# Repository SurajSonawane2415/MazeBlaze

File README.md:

# MazeBlaze
Develop a Line following and Maze Solving bot based on PID controller that can find the shortest path in a given maze.

## Table of Contents

- [Project](#project)
   - [Table of Contents](#table-of-contents)
   - [About The Project](#about-the-project)
   - [PCB MODEL](#pcb-model)
   - [Demo](#demo)
   - [File Structure](#file-structure)
   - [Getting started](#getting-started)
   - [Future Work](#future-work)
   - [Contributors](#contributors)
   - [Resources](#resources)
   - [Acknowledgements](#acknowledgements)
   - [License](#license)

## About The Project
In this project, we will create a Line-following, Maze-solving bot that can find the shortest path in the given maze.

## Domains Explored
Artificial Intelligence, Embedded C, Control Systems, Graph Algorithms, Electronics and PCB Design

## Project Workflow
- Learning firmware development by completing [Firmware task](https://github.com/SurajSonawane2415/MazeBlaze/tree/main/task/suraj/firmware). And we also understand the firmware used in [SRA Wall-E](https://github.com/SRA-VJTI/Wall-E) and [MazeBlaze-v2](https://github.com/PritK99/MazeBlaze).
- Learning PCB design by completing the line sensor array [pcb_design](https://github.com/SurajSonawane2415/MazeBlaze/tree/main/task/suraj/pcb%20design) task.
- For bot design improvement we created a detailed sheet to make the bot design better. In which we added the advantages and disadvantages of many designs we've reviewed and chosen the best design for the MazeBlaze-v3 bot.
- PCB Design for MazeBlaze-v3 by considering all points to make the bot design better.
- Implementing left follow rule.
- Implementing path planning.
- Implementing dijkstra's algorithm.
- Implementing flood-fill algorithm.
## PCB MODEL

## Demo
### LFR algorithm(Left follow rule):

https://github.com/SurajSonawane2415/MazeBlaze/assets/129578177/a419bddd-6653-45e9-b566-6e79a6069aff

### Dijkstra's algorithm:

https://github.com/SurajSonawane2415/MazeBlaze/assets/129578177/57cf2437-57e8-468f-b269-db0ec31de83d

## File Structure

```
👨‍💻MazeBlaze-v3.1
├ 📂 Firmware
| └ 📂1_left_follow_rule //Contains code for left-follow-rule and path planning
| | ├ 📂main
| | |   ├ 📄1_left_follow_rule.c
| | |   └ 📄CMakeList.txt
| | ├ 📄CMakeList.txt
| ├ 📂2_Dijkstra //Contains code for dijkstra`s algorithm   
| └ 📂Components //Contains all the header and source files used in the project
|   ├ 📂include
|   ├ 📂src
|   ├ 📂esp-wifi-logger
|   ├ 📄CMakeList.txt
├ 📂 assets
├ 📂 documentation //Contains documentation of the project.
├ 📂 pcb_design //Contains pcb_design files of MazeBlaze-v3 board
├ 📂 task
  ├ 📂 Atharv
  | ├ 📂 firmware 
  | |  └📂 1_led_blink.c
  | |    ├ 📂main
  | |    |   ├ 📄1_led_blink.c
  | |    |  └ 📄CMakeList.txt
  | |    ├ 📄CMakeList.txt
  | ├ 📂 pcb_design
  ├ 📂 Suraj
    ├ 📂 firmware //Conatins led blink task files and documentation of the task
    |  └📂 1_led_blink.c 
    |    ├ 📂main
    |    |   ├ 📄1_led_blink.c
    |    |   └ 📄CMakeList.txt
    |    ├ 📄CMakeList.txt
    |    ├ 📄README.md
    ├ 📂 pcb_design //Conatins lsa PCB design task files and documentation of the task
```
## Getting started
### Prerequisites
To download and use this code, the minimum requirements are:
- ESP_IDF
- Windows 7 or later (64-bit), Ubuntu 20.04 or later
- Microsoft VS Code or any other IDE

### Installation
Clone the project by typing the following command in your Terminal/CommandPrompt:
      
     `git clone https://github.com/SurajSonawane2415/MazeBlaze`

Navigate to the MazeBlaze folder:
`cd MazeBlaze`

### Usage

Once the requirements are satisfied, you can easily download the project and use it on your machine. After following the above steps, use the following commands to:

To activate the IDF:
`get_idf`

To build the code:
`idf.py build`

To flash the code:
`idf.py -p (PORT) flash monitor`

## Future Work
- [ ] Implementing better algorithms like DFS/BFS.
- [ ] Achieve higher speeds by increasing the efficiency of the bot.

## Contributors
- [Suraj Sonawane](https://github.com/SurajSonawane2415)
- [Atharva Nerkar](https://github.com/ARN1954)

## Resources
- [MazeBlaze-v2](https://github.com/PritK99/MazeBlaze) GitHub repository of MazeBlaze-v2 
- [MazeBlaze-v1](https://github.com/ChinmayLonkar/MAZEBLAZE) GitHub repository of MazeBlaze-v1
- [Dikstra's](https://www-geeksforgeeks-org.cdn.ampproject.org/v/s/www.geeksforgeeks.org/printing-paths-dijkstras-shortest-path-algorithm/amp/?usqp=mq331AQIUAKwASCAAgM%3D&amp_js_v=a9&amp_gsa=1#referrer=https%3A%2F%2Fwww.google.com&csi=1&ampshare=https%3A%2F%2Fwww.geeksforgeeks.org%2Fprinting-paths-dijkstras-shortest-path-algorithm%2Famp%2F%23referrer%3Dhttps%253A%252F%252Fwww.google.com%26csi%3D1%26ampshare%3Dhttps%253A%252F%252Fwww.geeksforgeeks.org%252Fprinting-paths-dijkstras-shortest-path-algorithm%252F) Implementation of dijkstr's algorithm in c.
- [Floodfill](https://github.com/Isuru-Dissanayake/piccola) Implementation of the Floodfill algorithm (simulation).

## Acknowledgements 
- [SRA VJTI](https://sravjti.in/) Eklavya 2023
- Special thanks to our mentors [Raj Gupta](https://github.com/RajGupta17), [Prit Kanadiya](https://github.com/PritK99), and all the seniors at SRA, VJTI for their constant support and guidance throughout the project.

## License
[MIT License](https://opensource.org/license/mit/)

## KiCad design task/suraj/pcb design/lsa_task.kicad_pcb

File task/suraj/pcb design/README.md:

# PCB Design Task:
In this task I designed a PCB for line sensor array(LSA) used in [SRA board](https://github.com/SRA-VJTI/sra-board-hardware-design). 
## Board images:
- Front side:
  
- Back side:

## Routing:
For routing of the control circuitry and power connections we used traces of 0.3mm width.
- Back copper routing

## Overview:
The Line Sensor Array (LSA) uses TCRT 5000 sensors to detect white and black lines on the surface. It then sends this data to the ESP-32 microcontroller. By analyzing and processing the data, the microcontroller ESP-32 accomplishes the task of line following.

## TCRT 5000
The TCRT 5000 is an optical sensor module commonly used for detecting the presence of objects or lines. It consists of an infrared (IR) emitter and a phototransistor. The emitter emits infrared light, which bounces off objects or surfaces and is detected by the phototransistor. The amount of reflected light is used to determine the proximity of an object or the presence of a surface, typically a white or black line. TCRT 5000 sensors are often employed in applications like line-following bot.

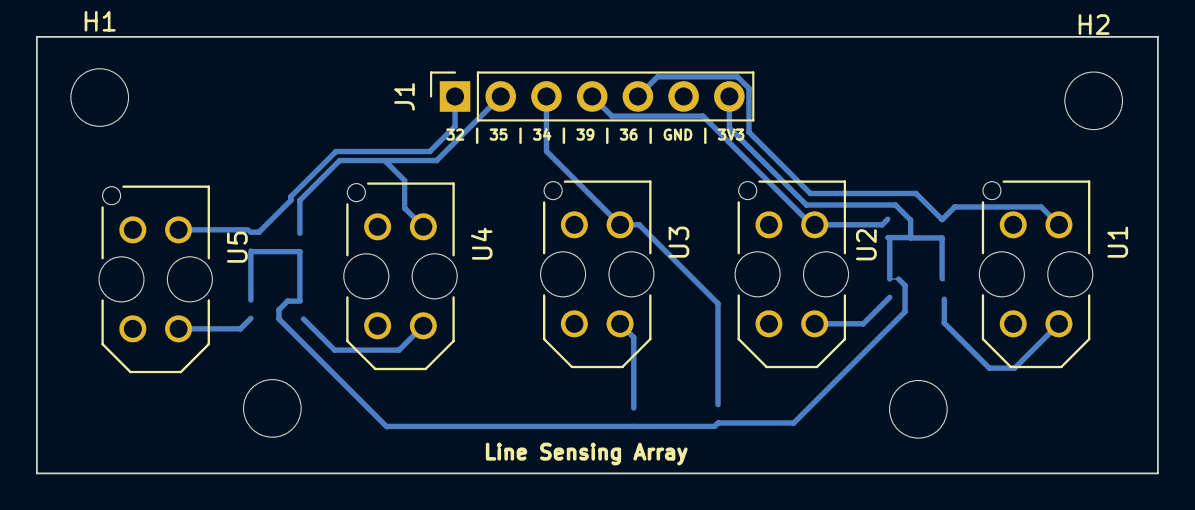
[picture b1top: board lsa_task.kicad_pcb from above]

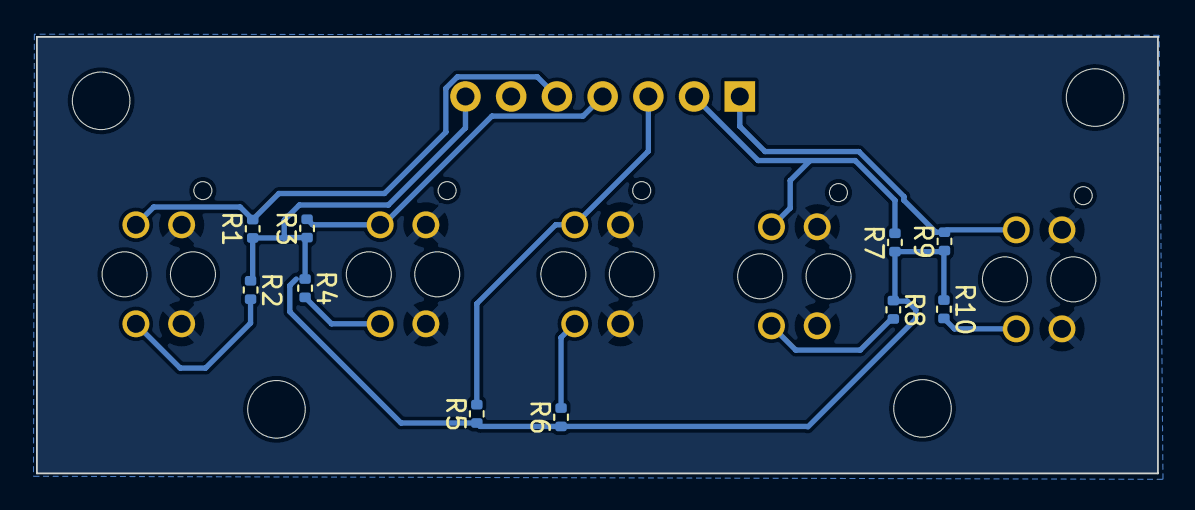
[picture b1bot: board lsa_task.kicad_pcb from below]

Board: 2 copper layers, 62.3 x 24.2 mm, 20 parts (10 on the bottom side), 12 nets.

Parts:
H1, H2, H3, H4: MountingHole_Pad; MountingHole_3.2mm_M3
J1: Conn_01x07_Pin; PinSocket_1x07_P2.54mm_Vertical
R1, R3, R5, R7, R9: 4k7; R_0402_1005Metric
R2, R4, R6, R8, R10: 1K; R_0402_1005Metric
U1, U2, U3, U4, U5: TCRT5000; OPTO_TCRT5000

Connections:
3V3: J1.7, R1.1, R2.1, R3.1, R4.1, R5.1, R6.1, R7.1, R8.1, R9.1, R10.1
A0_36: J1.5, R1.2, U1.COLL
A1_39: J1.4, R3.2, U2.COLL
A2_34: J1.3, R5.2, U3.COLL
A3_35: J1.2, R7.2, U4.COLL
A4_32: J1.1, R9.2, U5.COLL
GND: J1.6, U1.CATH, U1.E, U2.CATH, U2.E, U3.CATH, U3.E, U4.CATH, U4.E, U5.CATH, U5.E
unnamed: R2.2, U1.A
unnamed: R4.2, U2.A
unnamed: R6.2, U3.A
unnamed: R8.2, U4.A
unnamed: R10.2, U5.A

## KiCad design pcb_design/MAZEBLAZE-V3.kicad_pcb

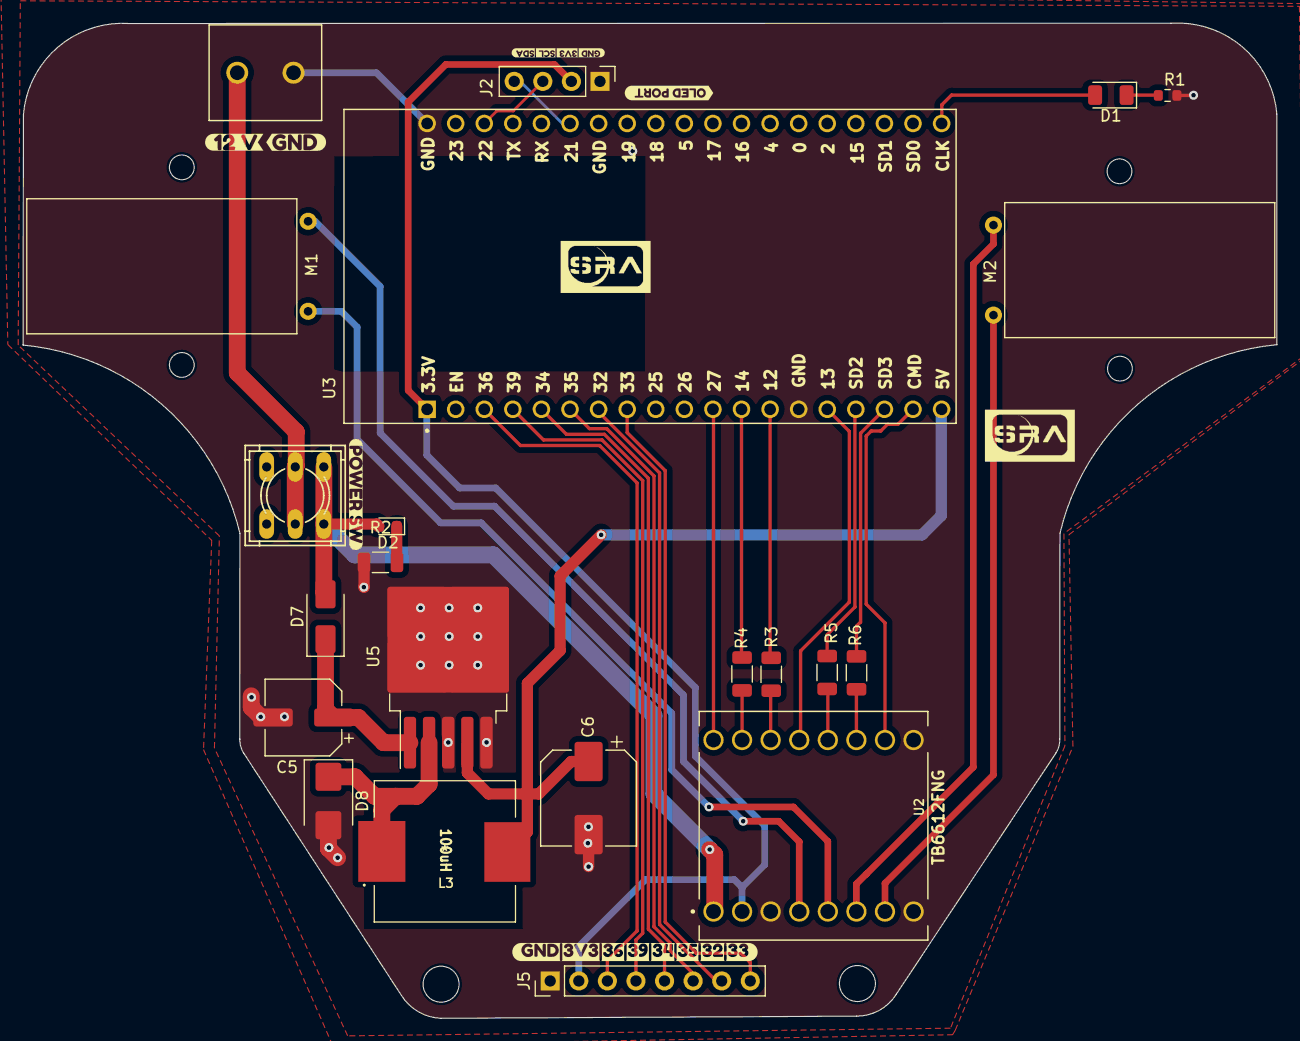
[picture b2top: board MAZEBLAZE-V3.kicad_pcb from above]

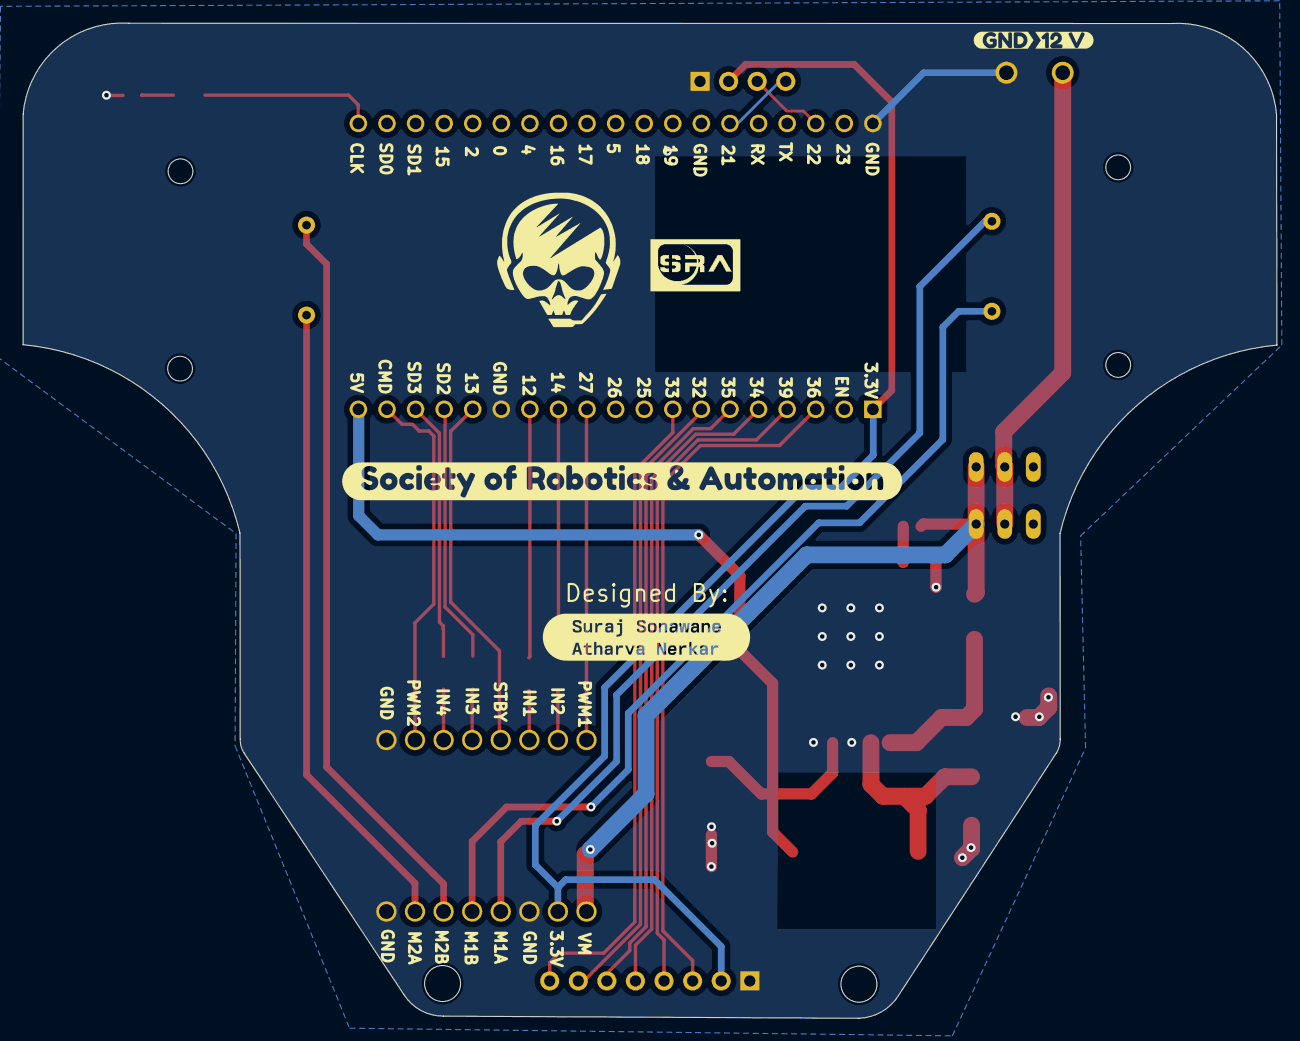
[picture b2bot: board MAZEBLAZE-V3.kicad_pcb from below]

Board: 2 copper layers, 111.4 x 88.4 mm, 38 parts (4 on the bottom side), 33 nets.

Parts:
12V_SW1: SW_Push_DPDT; dpdt_sw_2x03_tht
C5: 100uF; CP_Elec_6.3x7.7
C6: 470uF; CP_Elec_8x10
D1: RED-LED; LED_1206_3216Metric
D2: BLUE-POWER-LED; LED_0603_1608Metric
D7: SS24; D_SMA
D8: SS34; D_SMB
H1, H2#2, H3, H4: MountingHole; MountingHole_2.2mm_M2
H2, H5: MountingHole; MountingHole_3.2mm_M3
J1: Screw_Terminal_01x02; 12V_1x02_tht
J2: Conn_01x04_Pin; PinHeader_1x04_P2.54mm_Vertical
J5: Conn_01x08_Pin; PinHeader_1x08_P2.54mm_Vertical
L3: 100uH; CDRH127_inductor_smd
M1, M2: Motor_DC; N20_Motor
R1: 330; R_0603_1608Metric
R2: 1k5; R_1206_3216Metric
R3, R4, R5, R6: 1k; R_1206_3216Metric
U2: TB6612FNG; TB6612FNG_2
U3: ESP32-DEVKITC-32D; MODULE_ESP32-DEVKITC-32D
U5: LM2576S-5; TO-263-5_TabPin3
kibuzzard-61F7FB1D: G***; kibuzzard-61F7FB1D
kibuzzard-61F7FBA3: G***; kibuzzard-61F7FBA3
kibuzzard-61F7FBC2: G***; kibuzzard-61F7FBC2
kibuzzard-61F7147A: G***; kibuzzard-61F7147A
kibuzzard-61F71491: G***; kibuzzard-61F71491
kibuzzard-637A1A13: G***; kibuzzard-637A1A13
kibuzzard-653BE6A4: G***; kibuzzard-653BE6A4
kibuzzard-653BE7A2: G***; kibuzzard-653BE7A2
kibuzzard-653BEE79: G***; kibuzzard-653BEE79
kibuzzard-653E5949: G***; kibuzzard-653E5949

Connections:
3V3: J2.2, J5.2, U2.2 (VCC), U3.J2-1 (3V3)
5V: C6.1, L3.2, U3.J2-19 (EXT_5V), U5.4 (FB)
AIN1: R3.1, U3.J2-13 (IO12)
AIN2: R4.1, U3.J2-12 (IO14)
BIN1: R5.1, U3.J2-16 (SD2)
BIN2: R6.1, U3.J2-17 (SD3)
GND: C5.2, C6.2, D8.2 (A), J1.2, J2.1, J5.1, R1.2, R2.2, U2.3 (GND), U2.8 (GND), U2.9 (GND), U3.J2-14 (GND1), U3.J3-1 (GND3), U5.3 (GND), U5.5 (~ON/OFF)
IO23: D1.2 (A), U3.J3-19 (CLK)
unnamed: D1.1 (K), R1.1
unnamed: D2.1 (K), R2.1
unnamed: C5.1, D7.1 (K), U5.1 (VIN)
unnamed: D8.1 (K), L3.1, U5.2 (OUT)
unnamed: M1.1 (+), U2.4 (A01)
unnamed: M1.2 (-), U2.5 (A02)
unnamed: M2.1 (+), U2.7 (B01)
unnamed: M2.2 (-), U2.6 (B02)
unnamed: R3.2, U2.14 (AI1)
unnamed: R4.2, U2.15 (AI2)
unnamed: R5.2, U2.12 (BI1)
unnamed: R6.2, U2.11 (BI2)
PWMA: U2.16 (PWMA), U3.J2-11 (IO27)
PWMB: U2.10 (PWMB), U3.J2-18 (CMD)
SCL: J2.3, U3.J3-3 (IO22)
SDA: J2.4, U3.J3-6 (IO21)
SENS1: J5.3, U3.J2-3 (SENSOR_VP)
SENS2: J5.4, U3.J2-4 (SENSOR_VN)
SENS3: J5.5, U3.J2-5 (IO34)
SENS4: J5.6, U3.J2-6 (IO35)
SENS5: J5.7, U3.J2-7 (IO32)
SENS6: J5.8, U3.J2-8 (IO33)
STBY: U2.13 (STBY), U3.J2-15 (IO13)
VIN: 12V_SW1.2 (B), 12V_SW1.5 (B), J1.1
VIN_SW: 12V_SW1.3 (C), 12V_SW1.6 (C), D2.2 (A), D7.2 (A), U2.1 (VM)

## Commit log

2023-08-25 Rename Tasks/LFR Task/main.c to Tasks/Suraj/LFR_Task/main/main.c
2023-08-27 Create Tasks
2023-08-29 29 Aug 2023 EOD main.c
2023-08-30 30 AUG EOD main.c
2023-08-30 30 AUG EOD
    getting problem when node is detect. so to tacking left turn it goies into if statement. but for only one time
2023-09-06 Create main
2023-09-06 Update LFR.c
    updated left turn condition
2023-09-07 7 SEP EOD added extra condition for node detection.. and improve code.. but still bot not tacking turn and stop stabelly at a higher speed so extra condition needed
    7 SEP EOD added extra condition for node detection.. and improve code.. but still bot not tacking turn and stop stabelly at a higher speed so extra condition needed
2023-09-09 Only Right node condition is added
2023-09-10 Updated U turn logic and removed current reading function.. but bot not working stabelly
    Updated U turn(working properly) logic and removed current reading function.. but bot not working stabelly
2023-09-12 added LSA readings function before correction function in code. because bot not taking current readings for PID control
2023-09-13 Update LFR.c
    added LSA readings function before correction function in code. and removed unwanted 10 ms delay
2023-09-21 Counter method
2023-09-22 Updated Counter Method
2023-09-24 working code for all nodes
2023-09-24 Update code for all nodes
2023-09-25 Create simplify_path.c
    simplify path code
2023-09-26 Store path in array code
2023-09-27 Update simplify_path.c
    31 replaces by size
2023-09-27 Update LFR.c
    added simplify path condition and end condition
2023-09-29 Updated code with boot button function
2023-10-01 Updated final run code
2023-10-01 Updated final run function
2023-10-17 Update Final run code
    Tested code of full maze.
2023-10-20 Create Readme.md
    Started with documention
2023-10-20 Rename led_main.c to led_main.c
2023-10-21 Added errors description with solution
2023-10-21 Rename
2023-10-21 Create lsa
2023-10-22 code by using VISITED AND PARENT MATRIX
2023-10-23 Working code for 48×48 matrix
2023-10-24 Started implementation on hardware
2023-10-24 Delete
2023-10-24 create 1_ledblink task files
2023-10-24 update 1_ledblink
2023-10-26 Cost matrix is intialise in code.
2023-10-26 Update Error Descriptions and Solution
2023-10-26 Update error description and solutions
2023-10-26 Done with Final testing
2023-10-26 Create atharv
2023-10-27 Started with PCB design documentation
2023-10-27 Update PCB images
2023-10-28 Update final_straight() function
    We set a condition that makes the bot keep moving straight until the entire node is end (either the left or right sensor sees a white surface), which marks the end of a node. With this adjustment, th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
2023-10-28 added videos and snippet codes
2023-10-29 started new implemenation code with floodfill algorithm
2023-10-29 Update vieos
2023-10-30 Added firmware
2023-10-30 added new functions
2023-10-30 added some conditions to avoid miss identification of node
2023-10-30 Update PCB design documentation
2023-10-31 Updatefeatures of pcb4
2023-10-31 Update features of pcb
2023-10-31 Update lfr implementation part
2023-10-31 Added Major changes for PCB
2023-10-31 push pcb design files
2023-11-01 added code snipet
2023-11-01 upload lsa pcb design task
2023-11-01 push lsa task pcb design files
2023-11-01 push final lsa pcb design files
2023-11-02 Update PCB documentation
2023-11-02 add comments 1_ledblink.c
2023-11-02 added file stucture
2023-11-03 Upadte project workflow
2023-11-03 Create pcb task documentation
2023-11-03 added documentation for led blink task
2023-11-03 Create documentation for firmware task
2023-11-03 added pcb images and task videos
2023-11-03 added all the images of PCB design and implementation of algorithm videos.
2023-11-03 make readme
2023-11-03 Rename Readme.md to README.md
2023-11-03 Update Problems with current algorithm
2023-11-03 Fix typos and spelling errors in
2023-11-03 Fix typos and spelling errors in and addes licence
2023-11-03 Update file stucture
2023-11-04 push renamed task files
2023-11-04 Create
2023-11-04 pcb_design
2023-11-04 Update task README
2023-11-05 update pcb model
2023-11-08 tested code for maze traversal
2023-11-16 Update DEMO Video
2024-04-07 remove unnesessary
